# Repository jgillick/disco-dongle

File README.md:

# Disco Dongle

A USB to RS485 dongle uniquely designed for [Disco Bus](https://github.com/jgillick/Disco-Bus-Protocol)
networks, however, can be used for many other multidrop needs.

## About

This is a basic FTDI to RS485 device, that will connect your computer to a multidrop
network via USB. The RTS line is connected to RJ45 jack (ethernet jack) pin 3, and the DSR line is
connected to RJ45 jack pin 4.

If using this on a Disco Bus network, RTS/pin 3 would be to the first node's daisy chain line and
DSR/ping 4 would be on the shared signal line.

## Ethernet Pinout

The output of the dongle to the bus, is via a RJ45 ethernet jack.

| RJ45 Pin | Connection    |
|----------|---------------|
| 1        | RS485 A/Y     |
| 2        | RS485 B/Z     |
| 3        | RTS / Daisy   |
| 4        | DSR / Signal  |
| 5        | GND           |
| 6        | GND           |
| 7        | Not connected |
| 8        | Not connected |

### RTS & DSR Lines

The `RTS` and `DSR` serial lines are broken out to RJ45 pins 3 and 4, respectively.
They are pulled up by a pair of 20k resistors, and assumed enabled when driven low.
They also have LEDs used to determine their enabled state. The LED for `RTS` is labeled
"D" (for Daisy) and `DSR` is labeled "S" (for Signal).

## Power over the bus

Since pins 7 and 8 are unused, these can be used to send power to the bus, while
using pins 5 and 6 for ground.

## BOM

| QTY | Designator  | Value    | Footprint | Description       | Digikey |
|-----|-------------|----------|-----------|-------------------|---------|
| 4   | R1,R2,R4,R3 | 200      | 0805      | Resistor          | [RMCF0805JT200RCT-ND](https://www.digikey.com/product-detail/en/stackpole-electronics-inc/RMCF0805JT200R/RMCF0805JT200RCT-ND/1942543) |
| 3   | R5,R6,R8    | 20k      | 0805      | Resistor          | [311-20KARCT-ND](https://www.digikey.com/product-detail/en/yageo/RC0805JR-0720KL/311-20KARCT-ND/731229) |
| 1   | R7          | 120      | 0805      | Resistor          | [RMCF0805JT120R](http://www.digikey.com/product-detail/en/stackpole-electronics-inc/RMCF0805JT120R/RMCF0805JT120RCT-ND/1942540) |
| 3   | C1,C4,C5    | 100nF    | 0805      | Capacitor         | [1276-2450-1-ND](http://www.digikey.com/product-detail/en/samsung-electro-mechanics-america-inc/CL21B104MBCNNNC/1276-2450-1-ND/3890536) |
| 1   | C2          | 4.7uF    | 0805      | Capacitor         | [1276-6463-1-ND](http://www.digikey.com/product-detail/en/samsung-electro-mechanics-america-inc/CL21A475KOFNNNG/1276-6463-1-ND/5958091)|
| 1   | C3          | 10nF     | 0805      | Capacitor         | [1276-2434-1-ND](http://www.digikey.com/product-detail/en/samsung-electro-mechanics-america-inc/CL21B103KAANNNC/1276-2434-1-ND/3890520) |
| 2   | D1,D2       |          | 0805      | TX/RX LEDs        | [475-1415-1-ND](http://www.digikey.com/product-detail/en/osram-opto-semiconductors-inc/LH-R974-LP-1/475-1415-1-ND/1802604) |
| 2   | D3,D4       |          | 0805      | Daisy/Signal LEDs | [475-1410-1-ND](http://www.digikey.com/product-detail/en/osram-opto-semiconductors-inc/LG-R971-KN-1/475-1410-1-ND/1802598) |
| 1   | U1          |          | SSOP-28   | FT232RL           | [768-1007-1-ND](http://www.digikey.com/product-detail/en/ftdi-future-technology-devices-international-ltd/FT232RL-REEL/768-1007-1-ND/1836402) |
| 1   | U2          |          | SOIC-8    | RS485 Transceiver | [ISL81487EIBZ-TCT-ND](http://www.digikey.com/product-detail/en/intersil/ISL81487EIBZ-T/ISL81487EIBZ-TCT-ND/1034270) |
| 1   | J1          |          |           | USB - B Micro     | [609-4618-1-ND](http://www.digikey.com/product-search/en?keywords=609-4618-1-ND) |
| 1   | J2          |          |           | RJ45 Jack         | [609-1046-ND](http://www.digikey.com/product-search/en?keywords=54602-908LF) |

## Order One

You can either build one yourself, or [MacroFab](http://macrofab.com) will assemble
one for you for ~$30.

To use MacroFab:

 * [Create an account](http://macrofab.com)
 * Create a new PCB
 * Goto the "Design Files" tab.
   * Upload `BOM_MacroFab.xyrs`
   * Upload `Gerbers/*`
 * Goto the "Bill of Materials" tab and Verify all parts are selected/populated (except OSHW-Logo).
 * Goto the "Placement" tab and verify parts are arranged properly.
 * Click "Order Now"

## Credit

 This hardware was adapted from the [original work](https://github.com/cinderblock/DanceDongle)
 by [Cameron Tacklind](https://github.com/cinderblock).

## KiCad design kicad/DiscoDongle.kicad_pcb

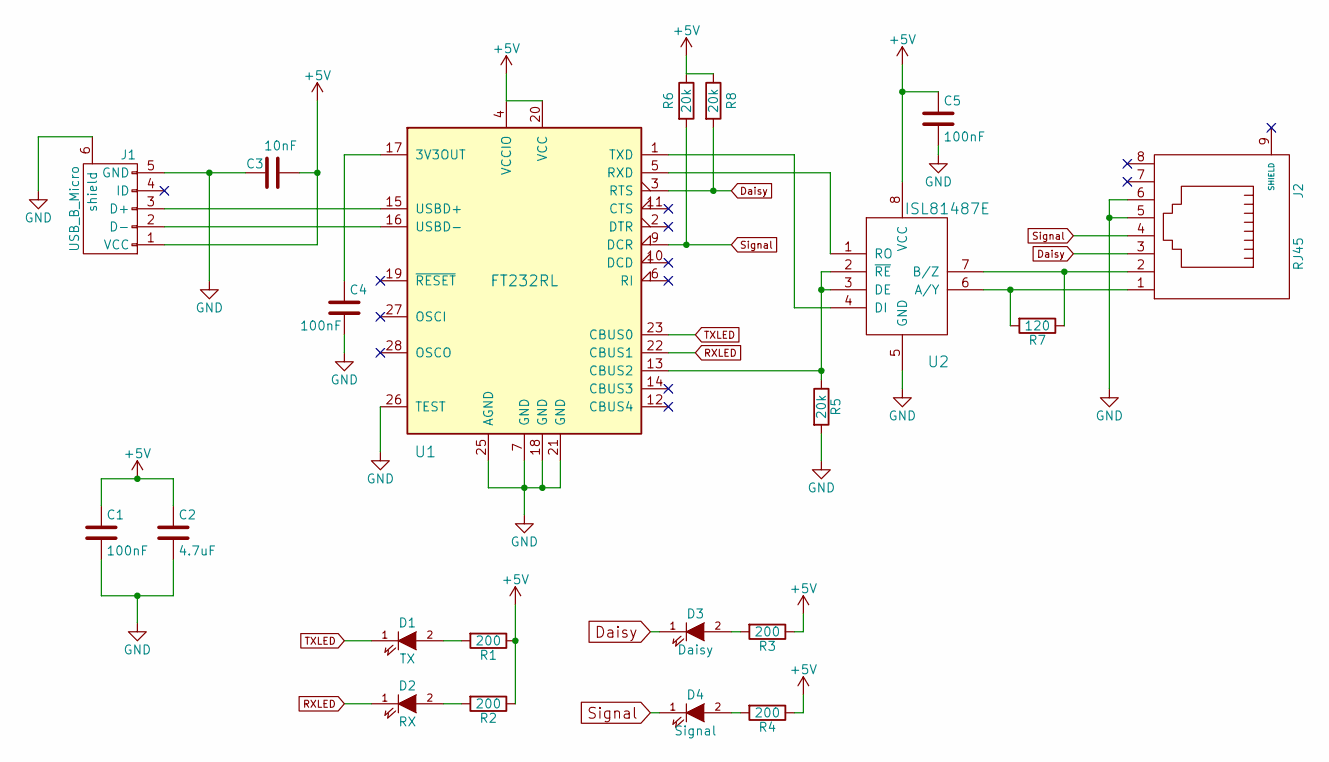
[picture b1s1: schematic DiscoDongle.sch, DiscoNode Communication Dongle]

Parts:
C1, C4, C5: 100nF; C_0805
C2: 4.7uF; C_0805; MPN CL21A475KOFNNNG; Digikey 1276-6463-1-ND
C3: 10nF; C_0805; MPN CL21B103KAANNNC; Digikey 1276-2434-1-ND
D1: TX; LED_0805; Digikey 475-1415-1-ND
D2: RX; LED_0805; Digikey 475-1415-1-ND
D3: Daisy; LED_0805; MPN LG R971-KN-1; Digikey 475-1410-1-ND
D4: Signal; LED_0805; MPN LG R971-KN-1; Digikey 475-1410-1-ND
J1: USB_B_Micro; USB_Micro-B; MPN 10118194-0001LF; Digikey 609-4618-1-ND
J2: RJ45; RJ45_8; MPN 54602-908LF; Digikey 609-1046-ND
R1, R2, R3, R4: 200; R_0805
R5, R6, R8: 20k; R_0805
R7: 120; R_0805; MPN RMCF0805JT120R; Digikey RMCF0805JT120RCT-ND
U1: FT232RL; SSOP-28_5.3x10.2mm_Pitch0.65mm; MPN FT232RL; Digikey 768-1007-1-ND
U2: ISL81487E; SOIC-8_3.9x4.9mm_Pitch1.27mm; Digikey ISL81487EIBZ-TCT-ND

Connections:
+5V: C1.1, C2.1, C3.1, C5.1, J1.1 (VCC), R1.1, R2.1, R3.1, R4.1, R6.1, R8.1, U1.4 (VCCIO), U1.20 (VCC), U2.8 (VCC)
Daisy: D3.1 (K), J2.3, R8.2, U1.3 (RTS)
GND: C1.2, C2.2, C3.2, C4.2, C5.2, J1.5 (GND), J1.6 (shield), J2.5, J2.6, R5.2, U1.7 (GND), U1.18 (GND), U1.21 (GND), U1.25 (AGND), U1.26 (TEST), U2.5 (GND)
unnamed: C4.1, U1.17 (3V3OUT)
unnamed: D1.2 (A), R1.2
unnamed: D2.2 (A), R2.2
unnamed: D3.2 (A), R3.2
unnamed: D4.2 (A), R4.2
unnamed: J1.2 (D-), U1.16 (USBD-)
unnamed: J1.3 (D+), U1.15 (USBD+)
unnamed: J2.1, R7.2, U2.6 (A/Y)
unnamed: J2.2, R7.1, U2.7 (B/Z)
unnamed: R5.1, U1.13 (CBUS2), U2.2 (~RE), U2.3 (DE)
unnamed: U1.1 (TXD), U2.4 (DI)
unnamed: U1.5 (RXD), U2.1 (RO)
RXLED: D2.1 (K), U1.22 (CBUS1)
Signal: D4.1 (K), J2.4, R6.2, U1.9 (DCR)
TXLED: D1.1 (K), U1.23 (CBUS0)

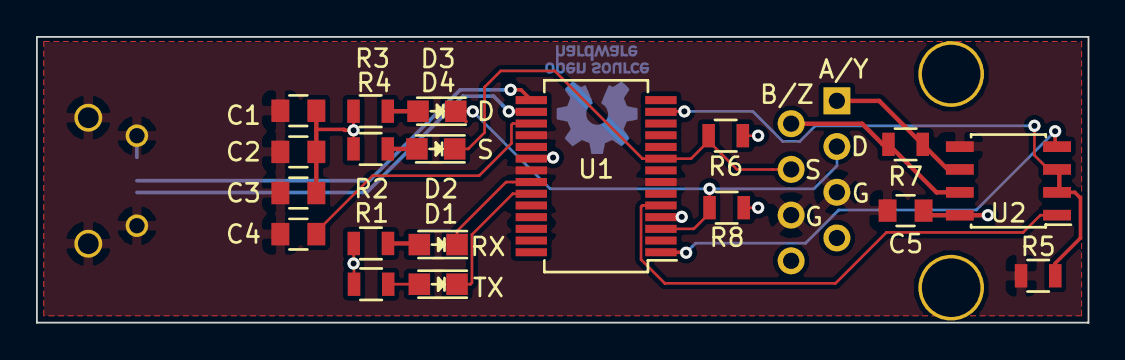
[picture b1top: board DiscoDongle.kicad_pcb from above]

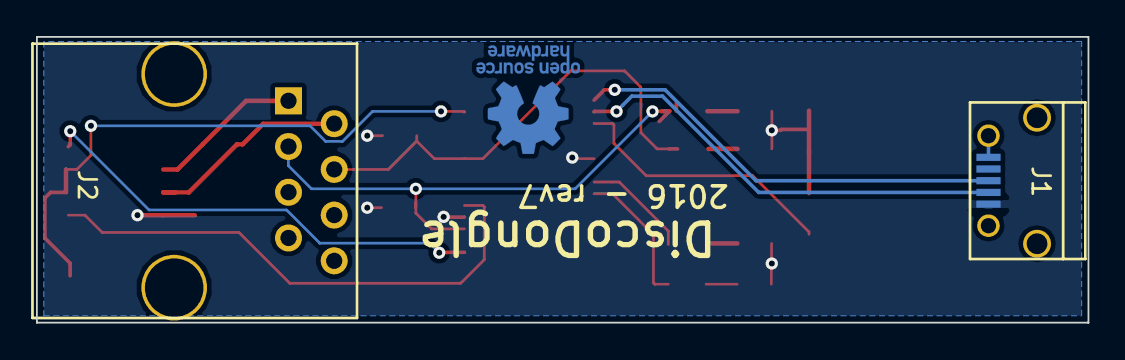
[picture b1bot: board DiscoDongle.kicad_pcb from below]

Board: 2 copper layers, 58.4 x 15.9 mm, 21 parts (2 on the bottom side), 18 nets.

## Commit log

2016-10-12 Add files
2016-10-12 Rename board
2016-10-12 Add OSHW badge
2016-10-22 Change USB to micro-B. Add part numbers
2017-06-26 Micro USB
